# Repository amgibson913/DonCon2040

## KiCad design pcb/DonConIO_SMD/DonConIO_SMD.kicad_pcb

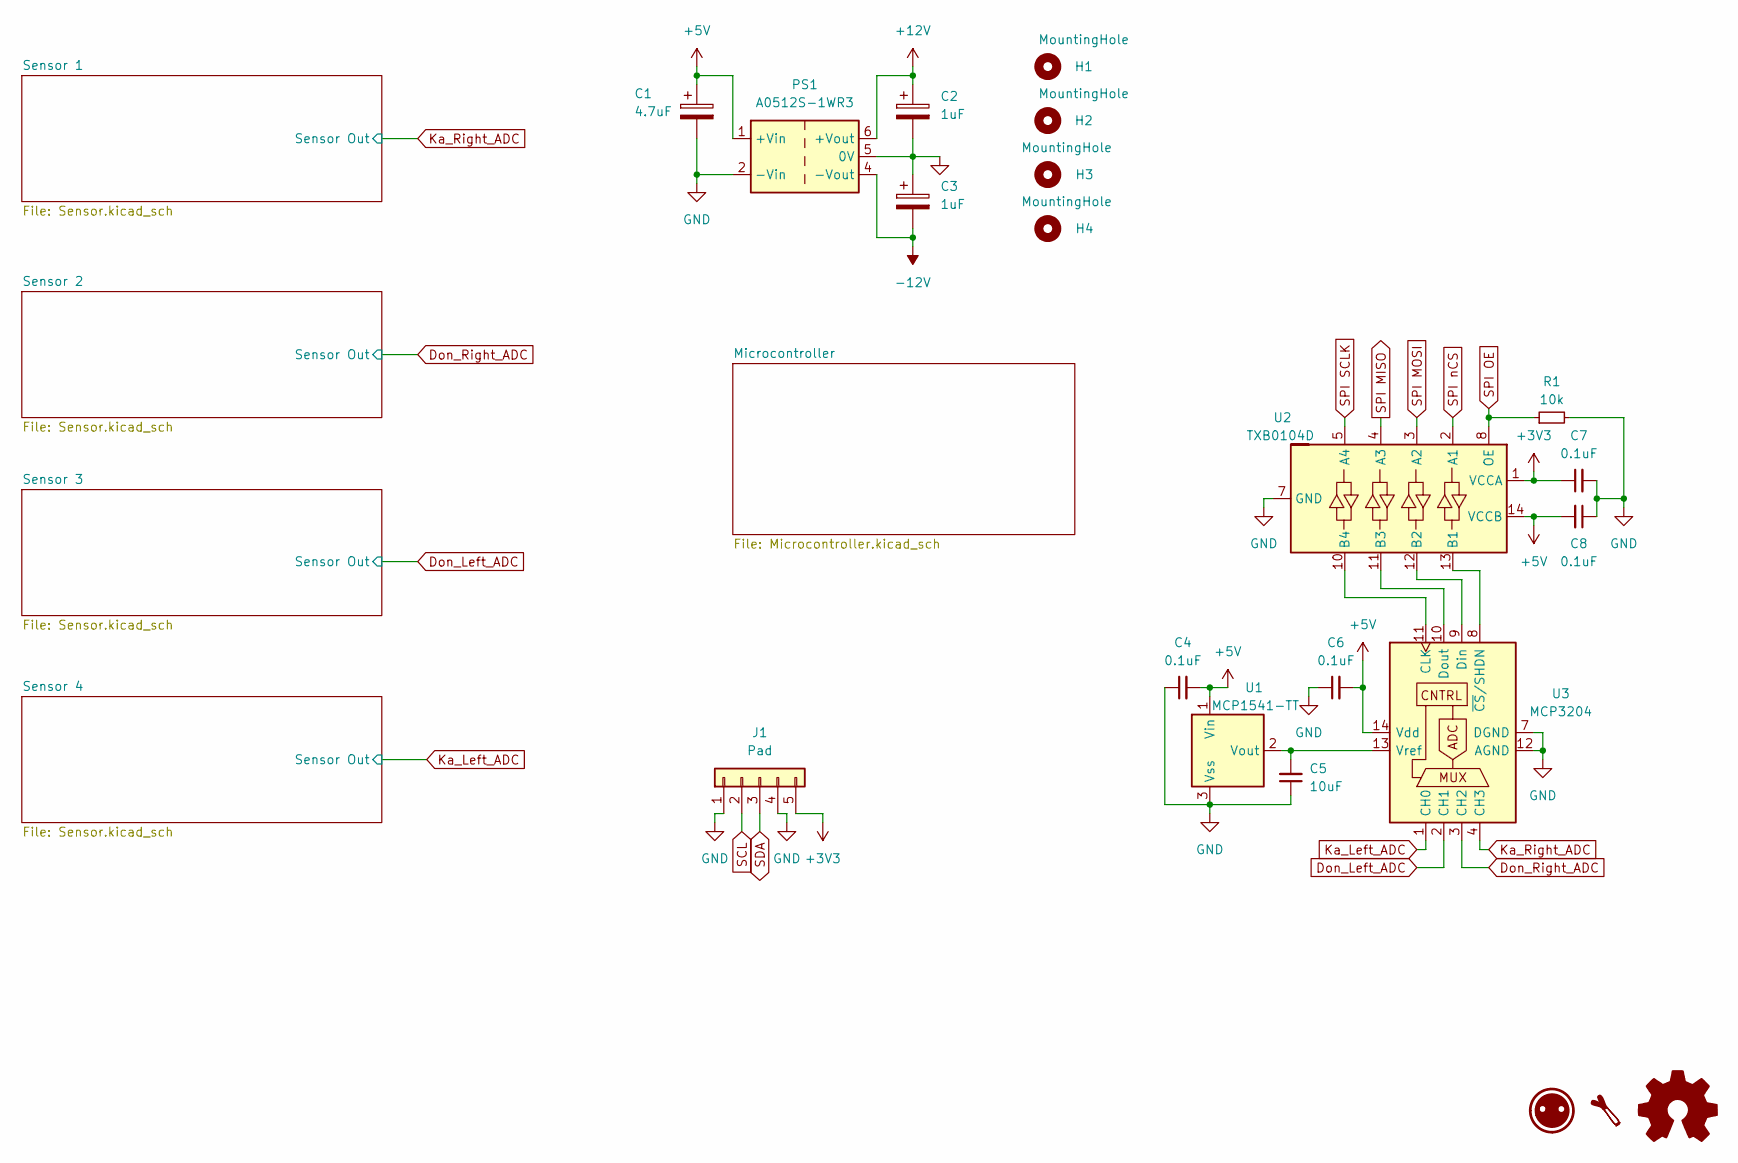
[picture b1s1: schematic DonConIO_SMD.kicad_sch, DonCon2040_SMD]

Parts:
C1: 4.7uF; C_0603_1608Metric
C2, C3: 1uF; C_0603_1608Metric
C4, C6, C7, C8: 0.1uF; C_0603_1608Metric
C5: 10uF; C_0603_1608Metric
H1, H2, H3, H4: MountingHole; MountingHole_3.2mm_M3
J1: Pad; JST_PH_S5B-PH-K_1x05_P2.00mm_Horizontal
PS1: A0512S-1WR3; Converter_DCDC_XP_POWER-IAxxxxS_THT
R1: 10k; R_0402_1005Metric
U1: MCP1541-TT; SOT-23
U2: TXB0104D; SOIC-14_3.9x8.7mm_P1.27mm
U3: MCP3204; SOIC-14_3.9x8.7mm_P1.27mm

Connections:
+3V3: C7.1, J1.5, U2.1 (VCCA); also elsewhere on the board
+5V: C1.1, C4.2, C6.2, C8.2, PS1.1 (+Vin), U1.1 (Vin), U2.14 (VCCB), U3.14 (Vdd); also elsewhere on the board
+12V: C2.1, PS1.6 (+Vout); also elsewhere on the board
-12V: C3.2, PS1.4 (-Vout); also elsewhere on the board
Don_Left_ADC: U3.2 (CH1); also elsewhere on the board
Don_Right_ADC: U3.3 (CH2); also elsewhere on the board
GND: C1.2, C2.2, C3.1, C4.1, C5.1, C6.1, C7.2, C8.1, J1.1, J1.4, PS1.2 (-Vin), PS1.5 (0V), R1.2, U1.3 (Vss), U2.7 (GND), U3.7 (DGND), U3.12 (AGND); also elsewhere on the board
Ka_Left_ADC: U3.1 (CH0); also elsewhere on the board
Ka_Right_ADC: U3.4 (CH3); also elsewhere on the board
unnamed: C5.2, U1.2 (Vout), U3.13 (Vref)
unnamed: U2.13 (B1), U3.8 (~CS/SHDN)
unnamed: U2.12 (B2), U3.9 (Din)
unnamed: U2.11 (B3), U3.10 (Dout)
unnamed: U2.10 (B4), U3.11 (CLK)
SCL: J1.2; also elsewhere on the board
SDA: J1.3; also elsewhere on the board
SPI MISO: U2.4 (A3); also elsewhere on the board
SPI MOSI: U2.3 (A2); also elsewhere on the board
SPI OE: R1.1, U2.8 (OE); also elsewhere on the board
SPI SCLK: U2.5 (A4); also elsewhere on the board
SPI nCS: U2.2 (A1); also elsewhere on the board

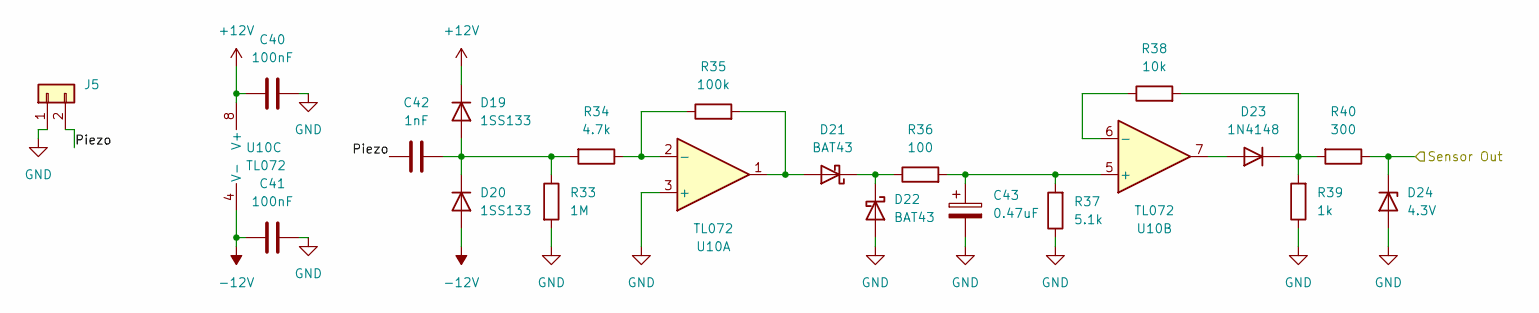
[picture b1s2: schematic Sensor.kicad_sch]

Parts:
C40, C41: 100nF; C_0402_1005Metric
C42: 1nF; C_0402_1005Metric
C43: 0.47uF; C_0402_1005Metric
D19, D20: 1SS133; D_0402_1005Metric
D21, D22: BAT43; D_0402_1005Metric
D23: 1N4148; D_0402_1005Metric
D24: 4.3V; D_0402_1005Metric
J5: JST; JST_PH_S2B-PH-K_1x02_P2.00mm_Horizontal
R33: 1M; R_0402_1005Metric
R34: 4.7k; R_0402_1005Metric
R35: 100k; R_0402_1005Metric
R36: 100; R_0402_1005Metric
R37: 5.1k; R_0402_1005Metric
R38: 10k; R_0402_1005Metric
R39: 1k; R_0402_1005Metric
R40: 300; R_0402_1005Metric
U10: TL072; SOIC-8_3.9x4.9mm_P1.27mm

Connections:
+12V: C40.1, D19.1 (K), U10.8 (V+); also elsewhere on the board
-12V: C41.1, D20.2 (A), U10.4 (V-); also elsewhere on the board
/Sensor 4/Piezo: C42.1, J5.2
GND: C40.2, C41.2, C43.2, D22.2 (A), D24.2 (A), J5.1, R33.2, R37.1, R39.1, U10.3 (+); also elsewhere on the board
Ka_Left_ADC: D24.1 (K), R40.1; also elsewhere on the board
unnamed: C42.2, D19.2 (A), D20.1 (K), R33.1, R34.2
unnamed: D21.2 (A), R35.2, U10.1
unnamed: D21.1 (K), D22.1 (K), R36.1
unnamed: D23.2 (A), U10.7
unnamed: D23.1 (K), R38.2, R39.2, R40.2
unnamed: R34.1, R35.1, U10.2 (-)
unnamed: C43.1, R36.2, R37.2, U10.5 (+)
unnamed: R38.1, U10.6 (-)

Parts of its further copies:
C28, C29, C32, C33, C36, C37: 100nF; C_0402_1005Metric
C30, C34, C38: 1nF; C_0402_1005Metric
C31, C35, C39: 0.47uF; C_0402_1005Metric
D1, D2, D7, D8, D13, D14: 1SS133; D_0402_1005Metric
D3, D4, D9, D10, D15, D16: BAT43; D_0402_1005Metric
D5, D11, D17: 1N4148; D_0402_1005Metric
D6, D12, D18: 4.3V; D_0402_1005Metric
J2, J3, J4: JST; JST_PH_S2B-PH-K_1x02_P2.00mm_Horizontal
R9, R17, R25: 1M; R_0402_1005Metric
R10, R18, R26: 4.7k; R_0402_1005Metric
R11, R19, R27: 100k; R_0402_1005Metric
R12, R20, R28: 100; R_0402_1005Metric
R13, R21, R29: 5.1k; R_0402_1005Metric
R14, R22, R30: 10k; R_0402_1005Metric
R15, R23, R31: 1k; R_0402_1005Metric
R16, R24, R32: 300; R_0402_1005Metric
U7, U8, U9: TL072; SOIC-8_3.9x4.9mm_P1.27mm

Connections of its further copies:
+12V: C28.1, C32.1, C36.1, D1.1 (K), D7.1 (K), D13.1 (K), U7.8 (V+), U8.8 (V+), U9.8 (V+); also elsewhere on the board
-12V: C29.1, C33.1, C37.1, D2.2 (A), D8.2 (A), D14.2 (A), U7.4 (V-), U8.4 (V-), U9.4 (V-); also elsewhere on the board
/Sensor 1/Piezo: C30.1, J2.2
/Sensor 2/Piezo: C34.1, J3.2
/Sensor 3/Piezo: C38.1, J4.2
Don_Left_ADC: D18.1 (K), R32.1; also elsewhere on the board
Don_Right_ADC: D12.1 (K), R24.1; also elsewhere on the board
GND: C28.2, C29.2, C31.2, C32.2, C33.2, C35.2, C36.2, C37.2, C39.2, D4.2 (A), D6.2 (A), D10.2 (A), D12.2 (A), D16.2 (A), D18.2 (A), J2.1, J3.1, J4.1, R9.2, R13.1, R15.1, R17.2, R21.1, R23.1, R25.2, R29.1, R31.1, U7.3 (+), U8.3 (+), U9.3 (+); also elsewhere on the board
Ka_Right_ADC: D6.1 (K), R16.1; also elsewhere on the board
unnamed: C30.2, D1.2 (A), D2.1 (K), R9.1, R10.2
unnamed: D3.2 (A), R11.2, U7.1
unnamed: D3.1 (K), D4.1 (K), R12.1
unnamed: D5.2 (A), U7.7
unnamed: D5.1 (K), R14.2, R15.2, R16.2
unnamed: C34.2, D7.2 (A), D8.1 (K), R17.1, R18.2
unnamed: D9.2 (A), R19.2, U8.1
unnamed: D9.1 (K), D10.1 (K), R20.1
unnamed: D11.2 (A), U8.7
unnamed: D11.1 (K), R22.2, R23.2, R24.2
unnamed: C38.2, D13.2 (A), D14.1 (K), R25.1, R26.2
unnamed: D15.2 (A), R27.2, U9.1
unnamed: D15.1 (K), D16.1 (K), R28.1
unnamed: D17.2 (A), U9.7
unnamed: D17.1 (K), R30.2, R31.2, R32.2
unnamed: R10.1, R11.1, U7.2 (-)
unnamed: C31.1, R12.2, R13.2, U7.5 (+)
unnamed: R14.1, U7.6 (-)
unnamed: R18.1, R19.1, U8.2 (-)
unnamed: C35.1, R20.2, R21.2, U8.5 (+)
unnamed: R22.1, U8.6 (-)
unnamed: R26.1, R27.1, U9.2 (-)
unnamed: C39.1, R28.2, R29.2, U9.5 (+)
unnamed: R30.1, U9.6 (-)

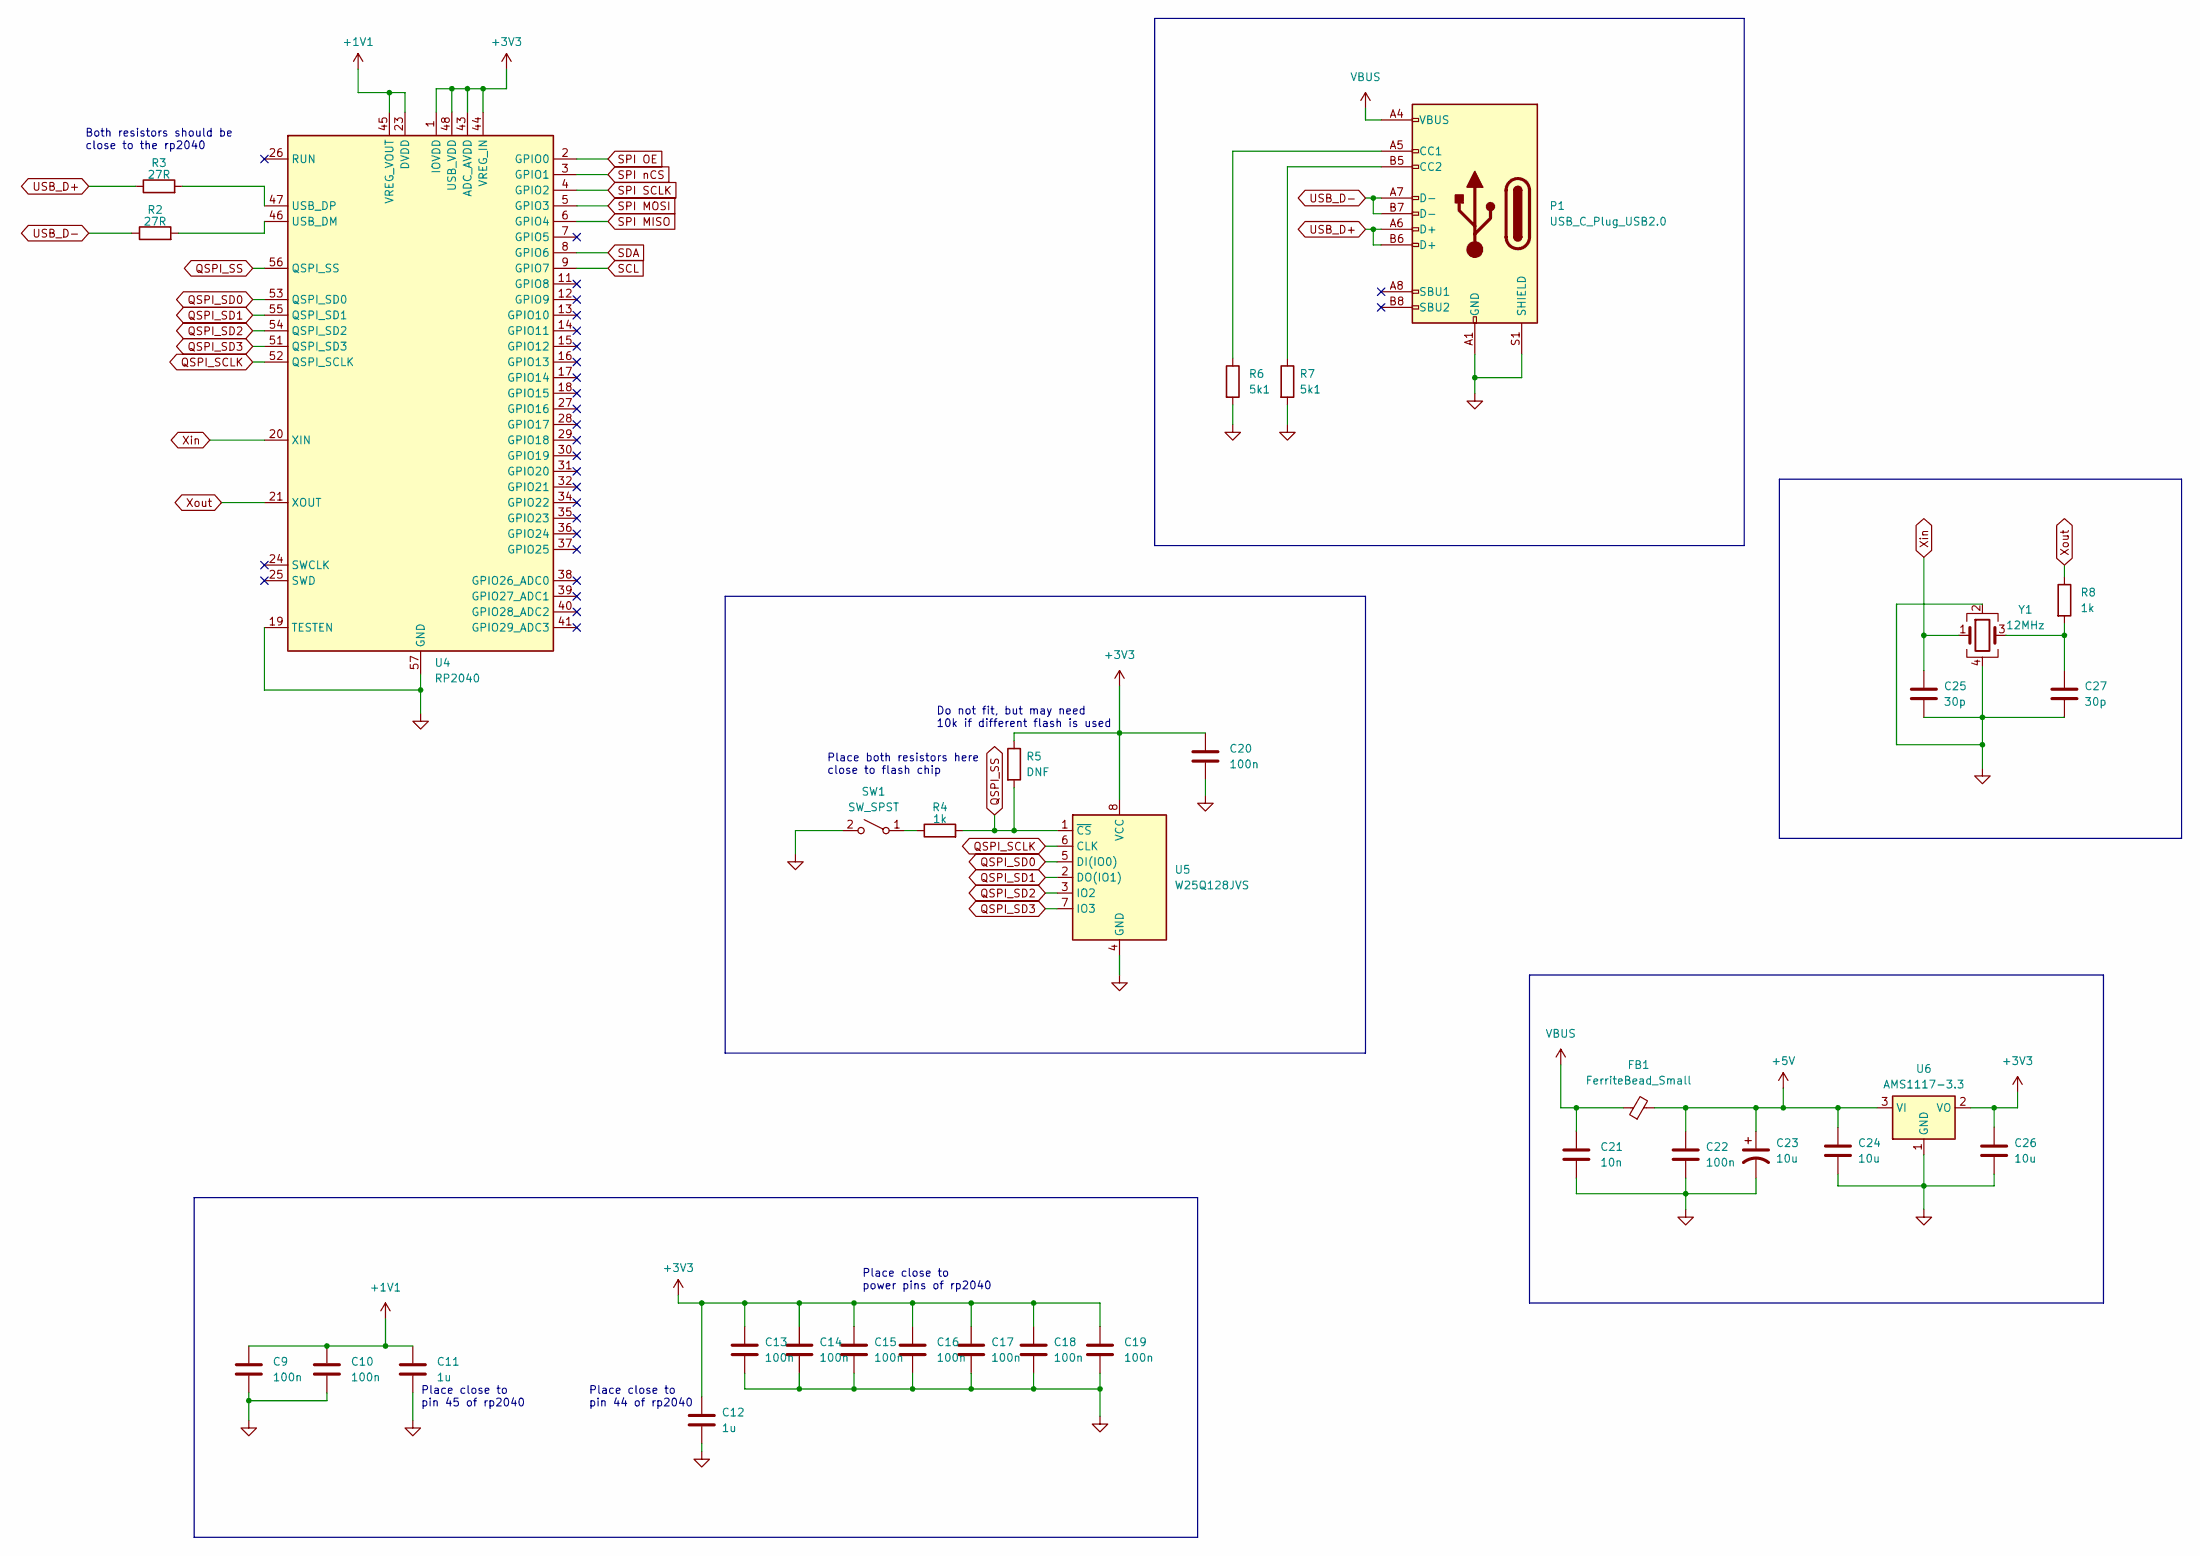
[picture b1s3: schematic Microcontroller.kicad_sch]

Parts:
C9, C10, C13, C14, C15, C16, C17, C18, C19, C20, C22: 100n; C_0402_1005Metric; MPN C1525
C11, C12: 1u; C_0603_1608Metric; MPN C15849
C21: 10n; C_0402_1005Metric; MPN C15195
C23: 10u; CP_EIA-3216-10_Kemet-I; MPN C7171
C24, C26: 10u; C_0805_2012Metric; MPN C15850
C25, C27: 30p; C_0402_1005Metric; MPN C1570
FB1: FerriteBead_Small; L_0805_2012Metric; MPN C1015
P1: USB_C_Plug_USB2.0; USB_C_Receptacle_G-Switch_GT-USB-7010ASV; MPN C2988369
R2, R3: 27R; R_0603_1608Metric; MPN C25190
R4, R8: 1k; R_0402_1005Metric; MPN C11702
R5: DNF; R_0402_1005Metric
R6, R7: 5k1; R_0402_1005Metric; MPN C25905
SW1: SW_SPST; SW_Push_1P1T_XKB_TS-1187A; MPN C318884
U4: RP2040; QFN-56-1EP_7x7mm_P0.4mm_EP3.2x3.2mm; MPN C2040
U5: W25Q128JVS; SOIC-8_5.23x5.23mm_P1.27mm; MPN C97521
U6: AMS1117-3.3; SOT-223-3_TabPin2; MPN C6186
Y1: 12MHz; Crystal_SMD_3225-4Pin_3.2x2.5mm; MPN C9002

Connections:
+1V1: C9.1, C10.1, C11.1, U4.23 (DVDD), U4.45 (VREG_VOUT), U4.50 (DVDD)
+3V3: C12.1, C13.1, C14.1, C15.1, C16.1, C17.1, C18.1, C19.1, C20.1, C26.1, R5.1, U4.1 (IOVDD), U4.10 (IOVDD), U4.22 (IOVDD), U4.33 (IOVDD), U4.42 (IOVDD), U4.43 (ADC_AVDD), U4.44 (VREG_IN), U4.48 (USB_VDD), U4.49 (IOVDD), U5.8 (VCC), U6.2 (VO); also elsewhere on the board
+5V: C22.1, C23.1, C24.1, FB1.2, U6.3 (VI); also elsewhere on the board
GND: C9.2, C10.2, C11.2, C12.2, C13.2, C14.2, C15.2, C16.2, C17.2, C18.2, C19.2, C20.2, C21.2, C22.2, C23.2, C24.2, C25.2, C26.2, C27.2, P1.A1 (GND), P1.A12 (GND), P1.B1 (GND), P1.B12 (GND), P1.S1 (SHIELD), R6.2, R7.2, SW1.2 (B), U4.19 (TESTEN), U4.57 (GND), U5.4 (GND), U6.1 (GND), Y1.2, Y1.4; also elsewhere on the board
unnamed: C27.1, R8.2, Y1.3
unnamed: P1.A5 (CC1), R6.1
unnamed: P1.B5 (CC2), R7.1
unnamed: R4.1, SW1.1 (A)
unnamed: R2.2, U4.46 (USB_DM)
unnamed: R3.2, U4.47 (USB_DP)
QSPI_SCLK: U4.52 (QSPI_SCLK), U5.6 (CLK)
QSPI_SD0: U4.53 (QSPI_SD0), U5.5 (DI(IO0))
QSPI_SD1: U4.55 (QSPI_SD1), U5.2 (DO(IO1))
QSPI_SD2: U4.54 (QSPI_SD2), U5.3 (IO2)
QSPI_SD3: U4.51 (QSPI_SD3), U5.7 (IO3)
QSPI_SS: R4.2, R5.2, U4.56 (QSPI_SS), U5.1 (~CS)
SCL: U4.9 (GPIO7); also elsewhere on the board
SDA: U4.8 (GPIO6); also elsewhere on the board
SPI MISO: U4.6 (GPIO4); also elsewhere on the board
SPI MOSI: U4.5 (GPIO3); also elsewhere on the board
SPI OE: U4.2 (GPIO0); also elsewhere on the board
SPI SCLK: U4.4 (GPIO2); also elsewhere on the board
SPI nCS: U4.3 (GPIO1); also elsewhere on the board
USB_D+: P1.A6 (D+), P1.B6 (D+), R3.1
USB_D-: P1.A7 (D-), P1.B7 (D-), R2.1
VBUS: C21.1, FB1.1, P1.A4 (VBUS), P1.A9 (VBUS), P1.B4 (VBUS), P1.B9 (VBUS)
Xin: C25.1, U4.20 (XIN), Y1.1
Xout: R8.1, U4.21 (XOUT)

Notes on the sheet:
Place both resistors here close to flash chip
Place close to power pins of rp2040
Do not fit, but may need 10k if different flash is used
Place close to pin 44 of rp2040
Both resistors should be close to the rp2040
Place close to pin 45 of rp2040

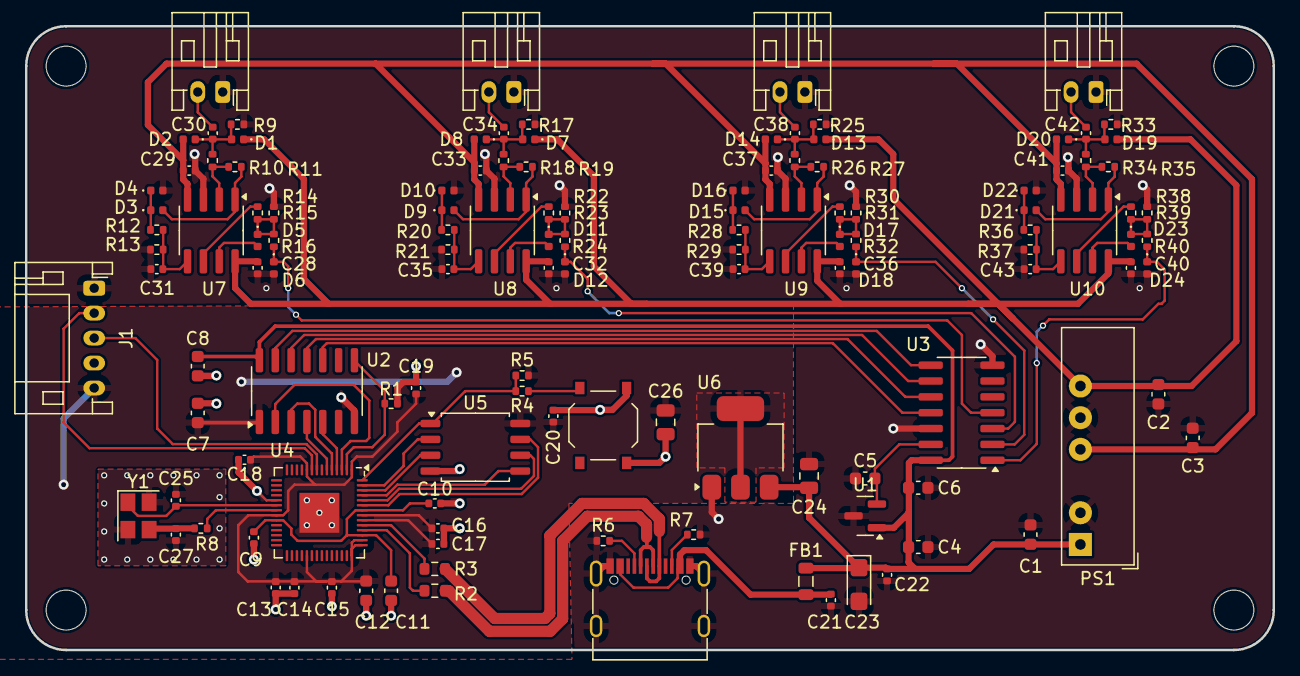
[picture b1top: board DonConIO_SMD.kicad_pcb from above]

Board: 2 copper layers, 100.0 x 50.0 mm, 131 parts (0 on the bottom side), 75 nets.

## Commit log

2024-06-10 First smd board commit
